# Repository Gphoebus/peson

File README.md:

# Visualiseur Mesure d'Effort – Arduino HX711
## Lycée de la Borde Basse

---

## 📦 Contenu du projet

```
mesure_effort/
├── arduino/
│   └── mesure_effort.ino       ← Sketch Arduino (à flasher sur le Nano)
├── python/
│   └── visualiseur_effort.py   ← Application PyQt5
├── requirements.txt
└── README.md
```

---

## 🔌 Matériel requis

| Composant | Connexion |
|-----------|-----------|
| Arduino Nano | USB PC |
| HX711 (jauge de contrainte) | DOUT=9, SCK=8 |
| Écran OLED SSD1306 128×64 I2C | SDA=A4, SCL=A5 |
| Encodeur rotatif | CLK=2, DT=3, SW=4 |

---

## 🖥️ Installation Python

```bash
pip install pyqt5 pyqtgraph pyserial
```

Ou avec le fichier requirements :

```bash
pip install -r requirements.txt
```

---

## 🚀 Utilisation

### 1. Arduino

1. Ouvrir `mesure_effort.ino` dans l'IDE Arduino
2. Installer les bibliothèques : `HX711_ADC`, `Adafruit_SSD1306`, `Adafruit_GFX`
3. Flasher sur l'Arduino Nano
4. Sur l'écran OLED, naviguer jusqu'à **Transmission** dans le menu
5. Appuyer sur le bouton de l'encodeur pour **démarrer/arrêter** la transmission

#### Les menus

### 2. Python

```bash
python visualiseur_effort.py
```

Sélectionner le port COM (Windows) ou `/dev/ttyUSB0` (Linux/Mac), choisir le baudrate **9600**, puis cliquer **Connecter**.

---

## 📡 Format de la trame USB

```
secondes;newtons\n
```

**Exemple :**
```
12.345;3.1416
25.000;0.0000
```

- `secondes` : temps écoulé depuis l'activation de la transmission (3 décimales)
- `newtons` : force mesurée (4 décimales), conversion : grammes × 9.80665 / 1000

---

## 💾 Sauvegarde CSV

Le fichier CSV généré utilise le point-virgule comme séparateur (compatible Excel français) :

```
N°;Temps (s);Effort (N)
1;1.000;0.4903
2;2.000;0.4905
...
```

---

## ⚙️ Menu Arduino

| Entrée menu | Action |
|-------------|--------|
| Tarer | Mise à zéro de la balance |
| Mesurer | Affichage en grammes et Newtons |
| Calibrer | Procédure de calibration (EEPROM) |
| **Transmission** | **Démarre/arrête l'envoi USB (1 trame/s)** |

> L'indicateur **[TX]** apparaît sur l'écran OLED tant que la transmission est active.

## Carte éléctronique

La carte électronique est conçue avec Kicad.
Vue Avant.

vue arrière avec un arduino NANO.

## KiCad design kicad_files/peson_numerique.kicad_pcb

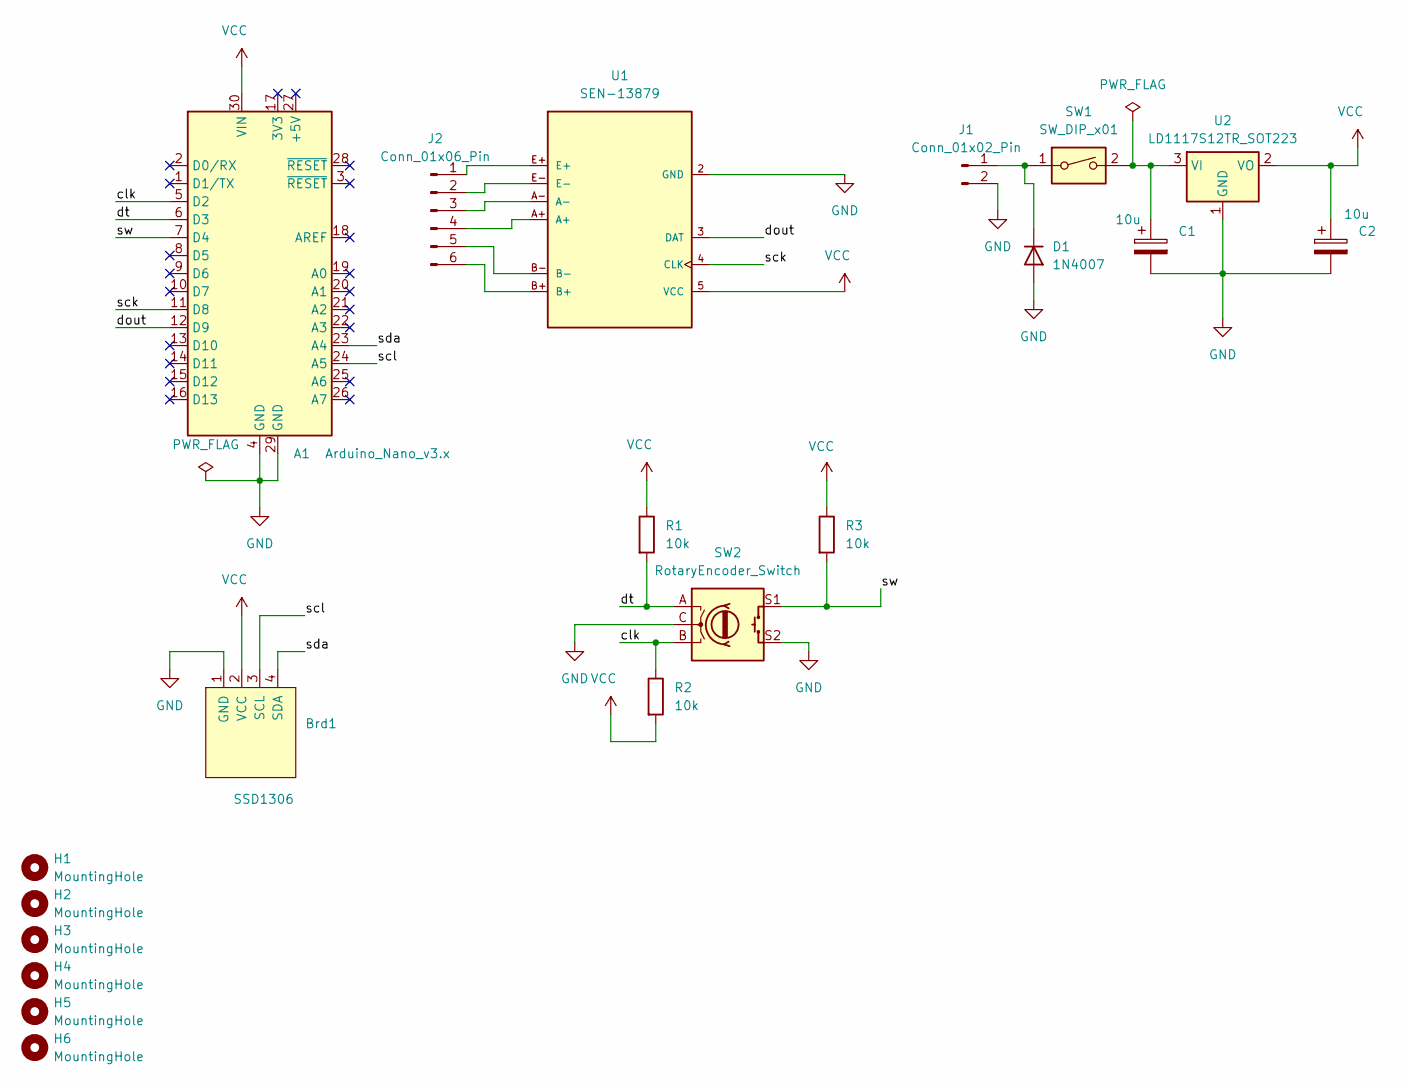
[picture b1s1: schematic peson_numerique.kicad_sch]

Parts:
A1: Arduino_Nano_v3.x; Arduino_Nano
Brd1: SSD1306; Adafruit_SSD1306
C1, C2: 10u; C_Disc_D3.4mm_W2.1mm_P2.50mm
D1: 1N4007; D_DO-41_SOD81_P10.16mm_Horizontal
H1, H2, H3, H4, H5, H6: MountingHole; MountingHole_3.2mm_M3
J1: Conn_01x02_Pin; PinHeader_1x02_P2.54mm_Vertical
J2: Conn_01x06_Pin; PinSocket_1x06_P2.54mm_Vertical
R1, R2, R3: 10k; R_Axial_DIN0207_L6.3mm_D2.5mm_P10.16mm_Horizontal
SW1: SW_DIP_x01; PinHeader_1x02_P2.54mm_Vertical
SW2: RotaryEncoder_Switch; XDCR_PEC11R-4020F-S0024
U1: SEN-13879; HX711
U2: LD1117S12TR_SOT223; SOT-223-3_TabPin2

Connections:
/clk: A1.5 (D2), R2.1, SW2.B
/dout: A1.12 (D9), U1.3 (DAT)
/dt: A1.6 (D3), R1.2, SW2.A
/sck: A1.11 (D8), U1.4 (CLK)
/scl: A1.24 (A5), Brd1.3 (SCL)
/sda: A1.23 (A4), Brd1.4 (SDA)
/sw: A1.7 (D4), R3.2, SW2.S1
GND: A1.4 (GND), A1.29 (GND), Brd1.1 (GND), C1.2, C2.2, D1.2 (A), J1.2, SW2.C, SW2.S2, U1.2 (GND), U2.1 (GND)
unnamed: D1.1 (K), J1.1, SW1.1
unnamed: J2.1, U1.E+
unnamed: J2.2, U1.E-
unnamed: J2.3, U1.A-
unnamed: J2.4, U1.A+
unnamed: J2.5, U1.B-
unnamed: J2.6, U1.B+
unnamed: C1.1, SW1.2, U2.3 (VI)
VCC: A1.30 (VIN), Brd1.2 (VCC), C2.1, R1.1, R2.2, R3.1, U1.5 (VCC), U2.2 (VO)

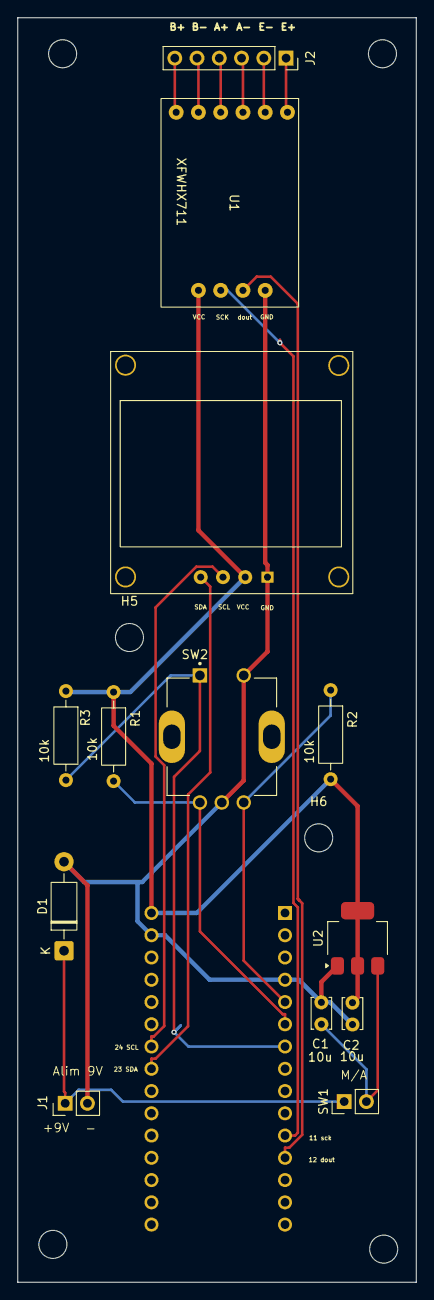
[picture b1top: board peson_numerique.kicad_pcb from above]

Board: 2 copper layers, 45.5 x 144.3 mm, 20 parts (1 on the bottom side), 17 nets.

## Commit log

2026-04-23 Debut
2026-04-23 Create README.md with project documentation
    Add project overview, installation instructions, and usage details for Arduino and Python applications.
2026-04-23 Create cao
2026-04-23 Update project author name in README
2026-04-24 pour le rendre executable
2026-04-24 Add image to README for project visualizationajout image
2026-04-24 Update README with electronic board information
    Added section about the electronic board design.
2026-04-24 Add images of electronic board in README
    Added images of the electronic board's front and back views.
2026-04-25 version 2.0
    Modification de la calibration et de la gestion du clic entre menu
2026-04-25 gestion menu
2026-04-25 Update README with menus section and image
    Added section on menus and included an image.
